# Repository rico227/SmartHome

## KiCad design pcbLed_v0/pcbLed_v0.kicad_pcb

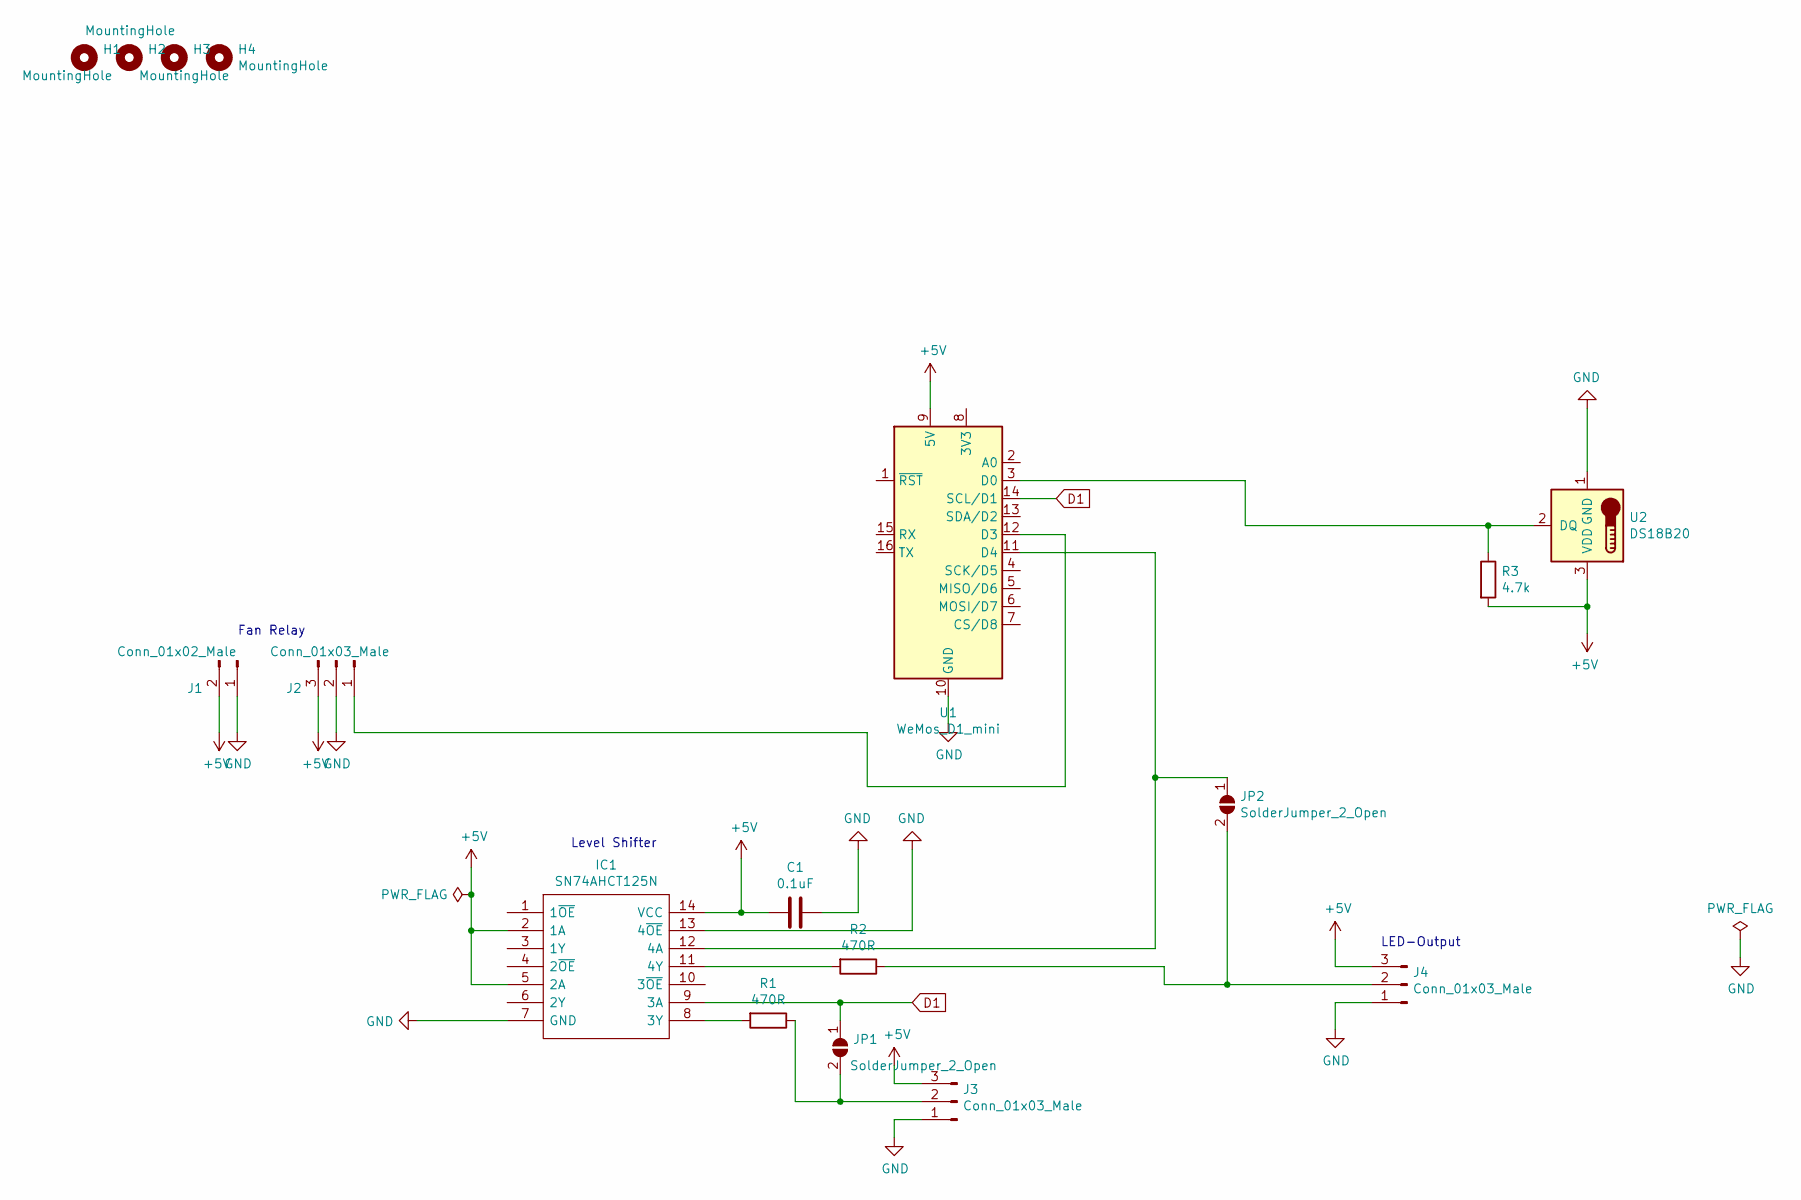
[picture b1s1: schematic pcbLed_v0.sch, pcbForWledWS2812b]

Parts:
C1: 0.1uF; C_1812_4532Metric_Pad1.57x3.40mm_HandSolder
H1, H2, H3, H4: MountingHole; MountingHole_3.2mm_M3_DIN965
IC1: SN74AHCT125N; DIP794W53P254L1930H508Q14N; Mouser Part Number 595-SN74AHCT125N
J1: Conn_01x02_Male; PinHeader_2x01_P2.54mm_Vertical
J2, J3, J4: Conn_01x03_Male; PinHeader_1x03_P2.54mm_Vertical
JP1, JP2: SolderJumper_2_Open; SolderJumper-2_P1.3mm_Open_Pad1.0x1.5mm
R1, R2: 470R; R_0402_1005Metric_Pad0.72x0.64mm_HandSolder
R3: 4.7k; R_0402_1005Metric_Pad0.72x0.64mm_HandSolder
U1: WeMos_D1_mini; WEMOS_D1_mini_light
U2: DS18B20; TO-92_Inline

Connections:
+5V: C1.2, IC1.2 (1A), IC1.5 (2A), IC1.14 (VCC), J1.2, J2.3, J3.3, J4.3, R3.2, U1.9 (5V), U2.3 (VDD)
D1: IC1.9 (3A), JP1.1 (A), U1.14 (SCL/D1)
GND: C1.1, IC1.7 (GND), IC1.13 (4~OE), J1.1, J2.2, J3.1, J4.1, U1.10 (GND), U2.1 (GND)
unnamed: IC1.8 (3Y), R1.2
unnamed: IC1.11 (4Y), R2.2
unnamed: IC1.12 (4A), JP2.1 (A), U1.11 (D4)
unnamed: J2.1, U1.12 (D3)
unnamed: J3.2, JP1.2 (B), R1.1
unnamed: J4.2, JP2.2 (B), R2.1
unnamed: R3.1, U1.3 (D0), U2.2 (DQ)

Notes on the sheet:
LED-Output
Level Shifter
Fan Relay

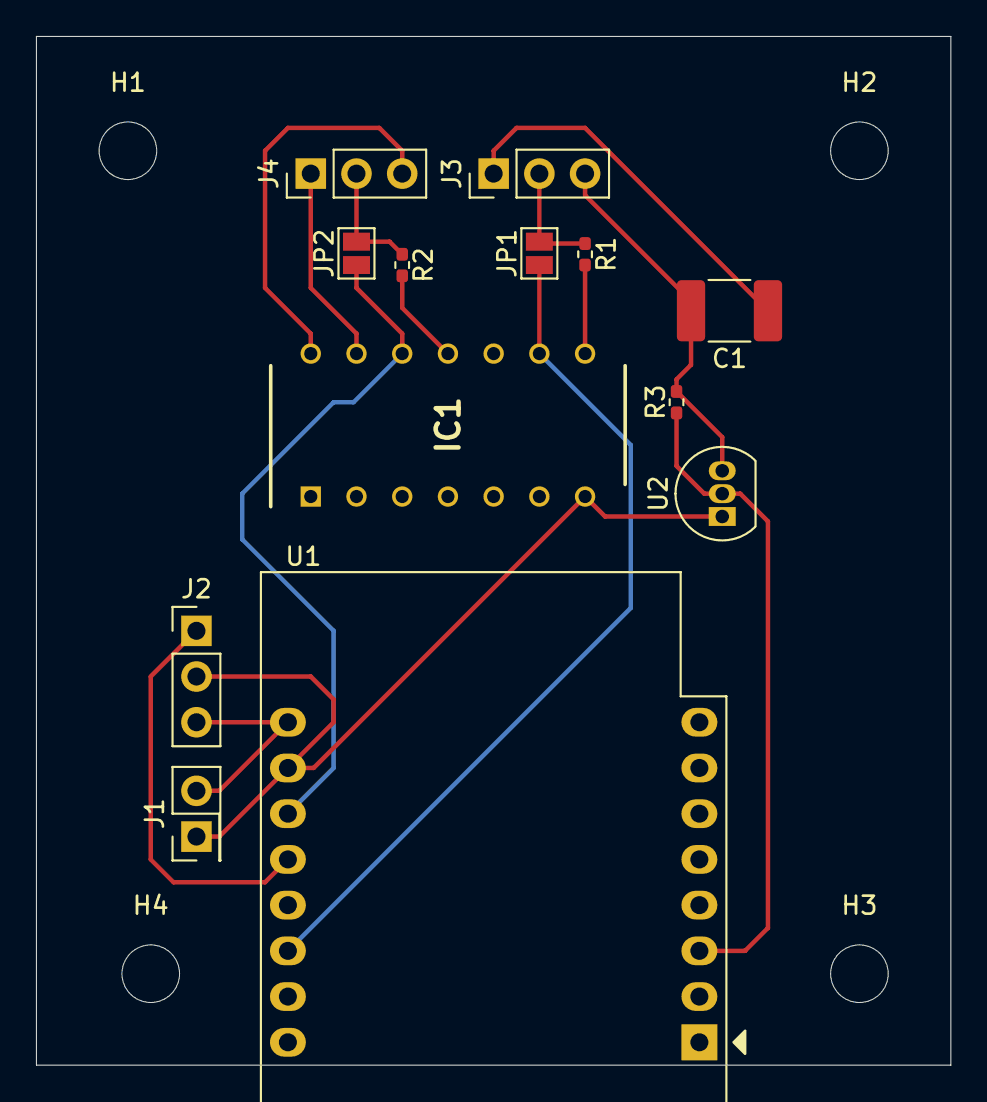
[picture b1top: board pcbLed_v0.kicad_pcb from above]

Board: 2 copper layers, 50.8 x 57.1 mm, 17 parts (0 on the bottom side), 10 nets.

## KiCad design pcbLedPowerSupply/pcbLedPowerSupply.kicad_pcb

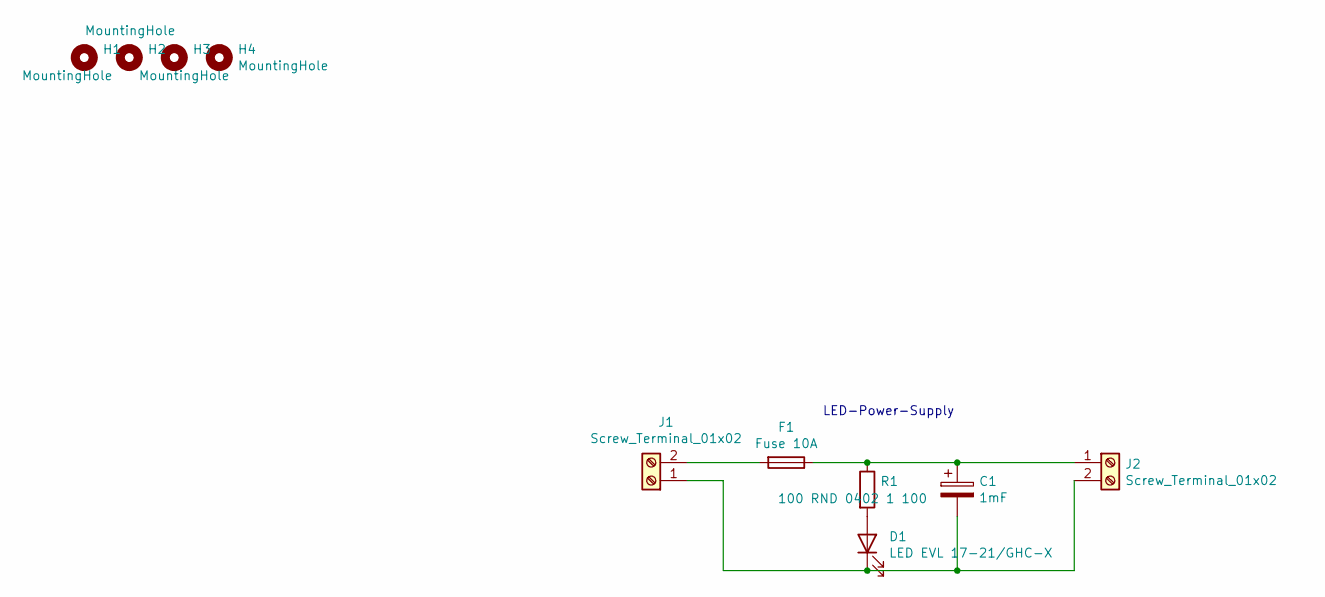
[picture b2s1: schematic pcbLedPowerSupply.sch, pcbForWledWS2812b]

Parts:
C1: 1mF; CP_Radial_D10.0mm_P5.00mm
D1: LED EVL 17-21/GHC-X; LED_0805_2012Metric_Pad1.15x1.40mm_HandSolder
F1: Fuse 10A; BELFUSE220043_10A_SMD2410
H1, H2, H3, H4: MountingHole; MountingHole_3.2mm_M3_DIN965
J1, J2: Screw_Terminal_01x02; TerminalBlock_Altech_AK300-2_P5.00mm
R1: 100 RND 0402 1 100; R_0402_1005Metric_Pad0.72x0.64mm_HandSolder

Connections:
unnamed: C1.1, F1.1, J2.1, R1.1
unnamed: C1.2, D1.1 (K), J1.1, J2.2
unnamed: D1.2 (A), R1.2
unnamed: F1.2, J1.2

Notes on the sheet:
LED-Power-Supply

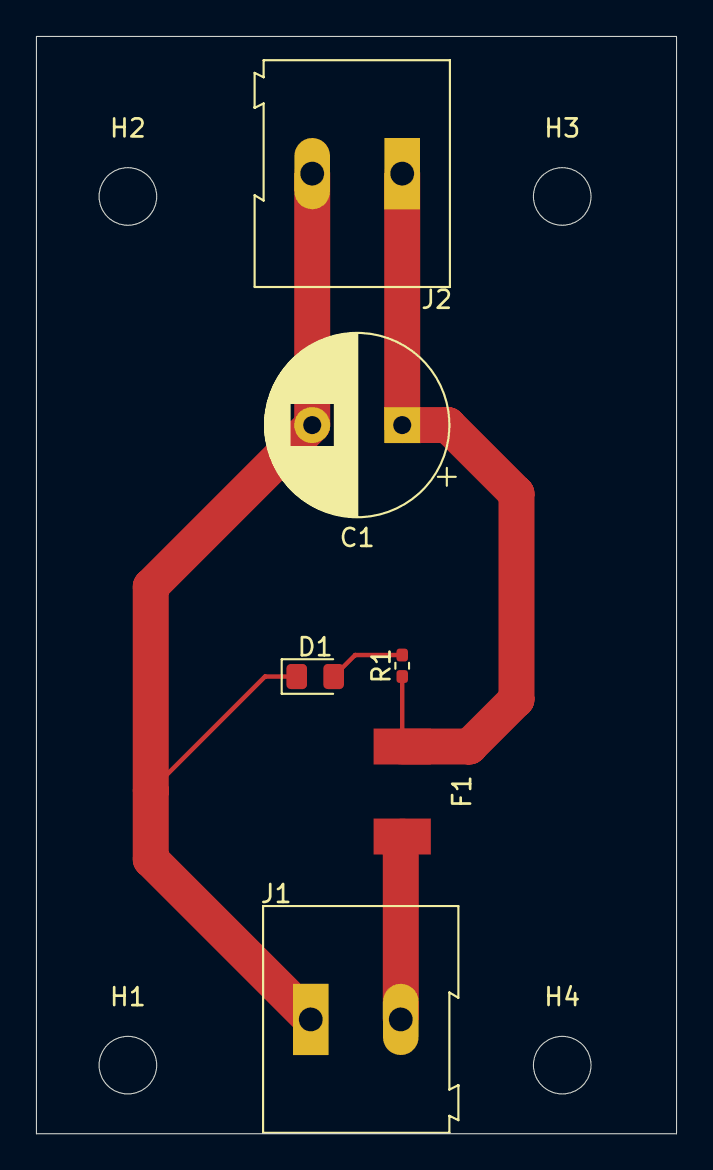
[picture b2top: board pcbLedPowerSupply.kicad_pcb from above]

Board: 2 copper layers, 35.6 x 61.0 mm, 10 parts (0 on the bottom side), 4 nets.

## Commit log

2021-04-08 init
2021-04-08 added existing folders
2021-04-15 prototyp with full power supply through pcb
2021-04-29 split to 2 pcbs; one for power supply; one for the other
